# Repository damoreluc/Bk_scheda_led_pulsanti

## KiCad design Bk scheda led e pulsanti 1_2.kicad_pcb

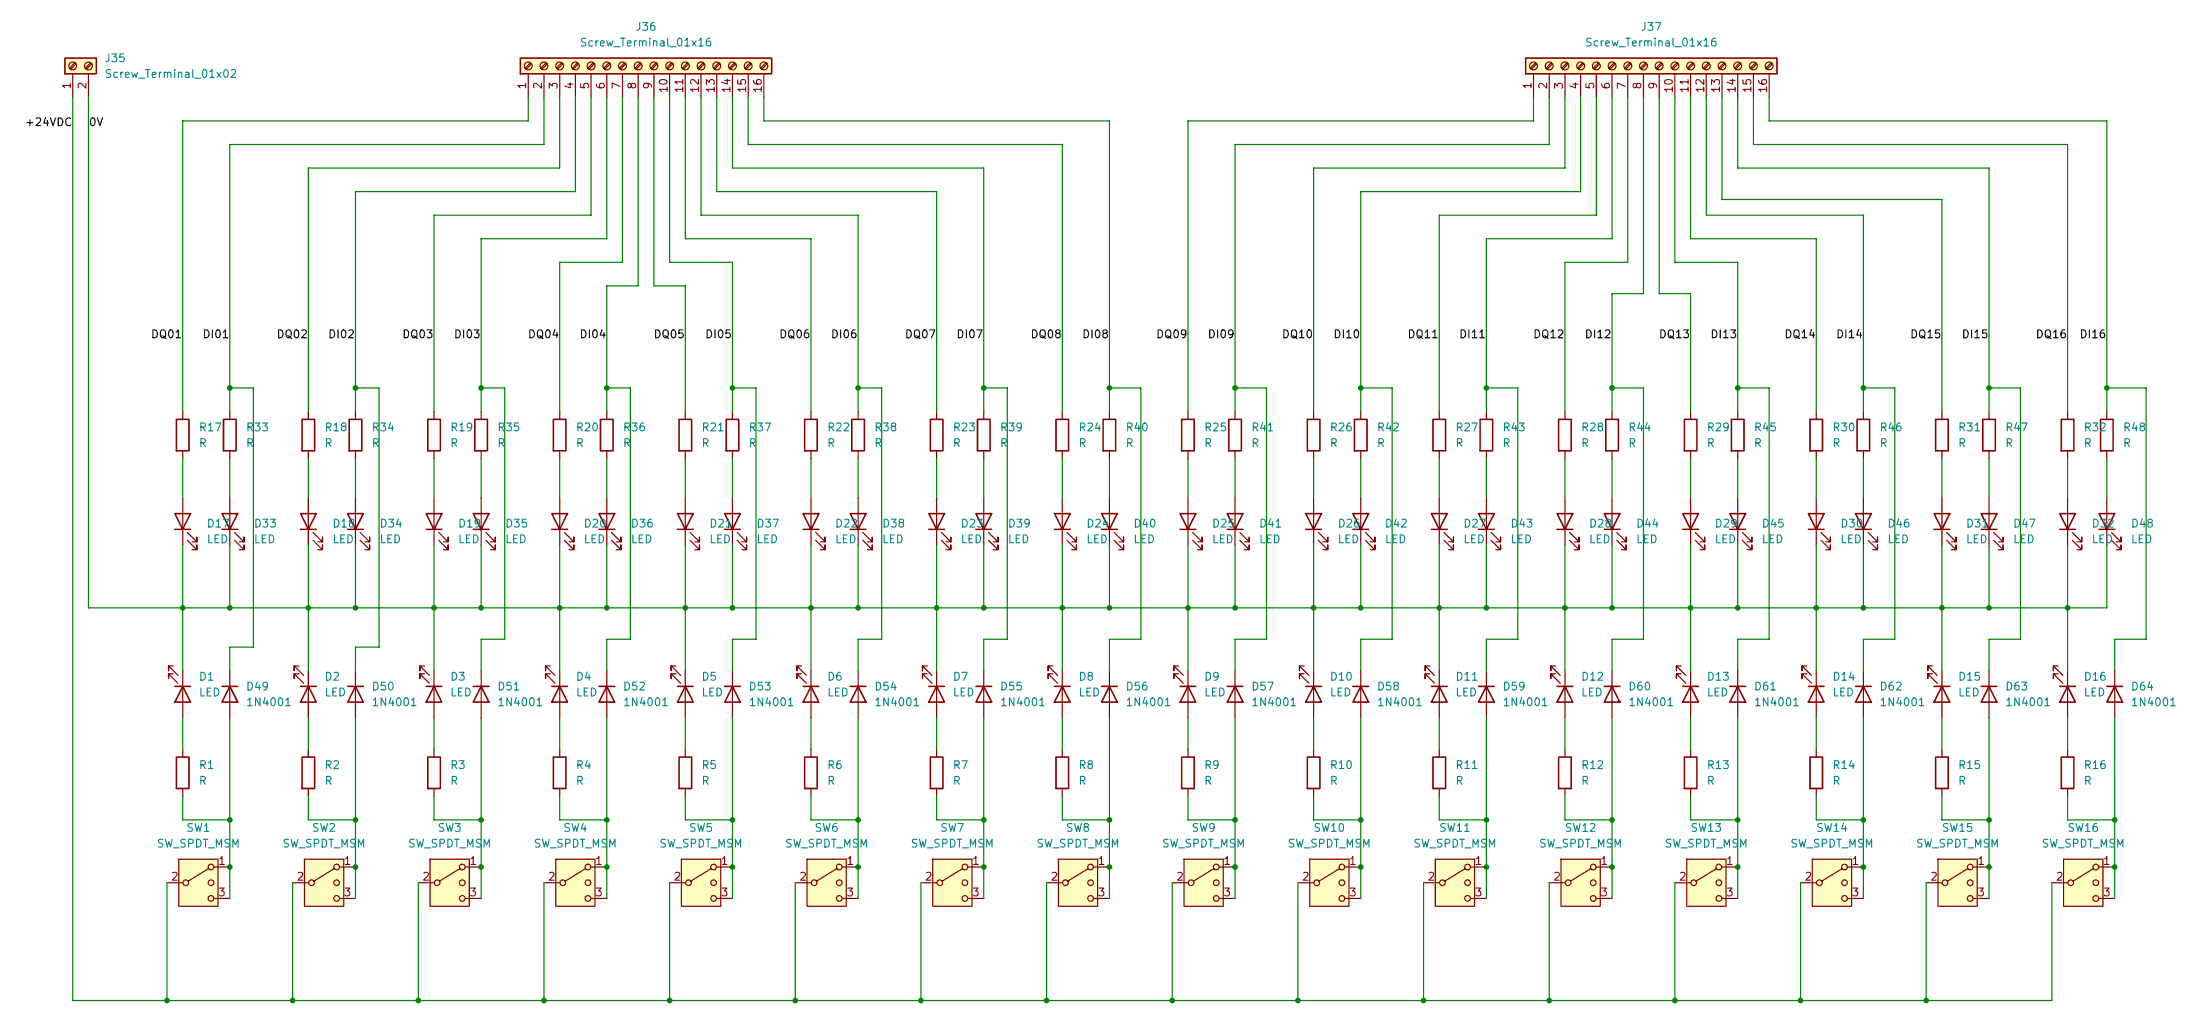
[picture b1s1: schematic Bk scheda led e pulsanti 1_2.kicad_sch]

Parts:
D1, D2, D3, D4, D5, D6, D7, D8, D9, D10, D11, D12, D13, D14, D15, D16, D17, D18, D19, D20, D21, D22, D23, D24, D25, D26, D27, D28, D29, D30, D31, D32, D33, D34, D35, D36, D37, D38, D39, D40, D41, D42, D43, D44, D45, D46, D47, D48: LED; LED_D5.0mm
D49, D50, D51, D52, D53, D54, D55, D56, D57, D58, D59, D60, D61, D62, D63, D64: 1N4001; D_DO-15_P12.70mm_Horizontal
J35: Screw_Terminal_01x02; TerminalBlock_Phoenix_PT-1,5-2-5.0-H_1x02_P5.00mm_Horizontal
J36, J37: Screw_Terminal_01x16; TerminalBlock_Phoenix_PT-1,5-16-5.0-H_1x16_P5.00mm_Horizont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
R1, R2, R3, R4, R5, R6, R7, R8, R9, R10, R11, R12, R13, R14, R15, R16, R17, R18, R19, R20, R21, R22, R23, R24, R25, R26, R27, R28, R29, R30, R31, R32, R33, R34, R35, R36, R37, R38, R39, R40, R41, R42, R43, R44, R45, R46, R47, R48: R; R_Axial_DIN0411_L9.9mm_D3.6mm_P12.70mm_Horizontal
SW1, SW2, SW3, SW4, SW5, SW6, SW7, SW8, SW9, SW10, SW11, SW12, SW13, SW14, SW15, SW16: SW_SPDT_MSM; SW_DEVIATORE_A_LEVETTAX03_D8X14_P4,70mm

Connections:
/0V: D1.1 (K), D2.1 (K), D3.1 (K), D4.1 (K), D5.1 (K), D6.1 (K), D7.1 (K), D8.1 (K), D9.1 (K), D10.1 (K), D11.1 (K), D12.1 (K), D13.1 (K), D14.1 (K), D15.1 (K), D16.1 (K), D17.1 (K), D18.1 (K), D19.1 (K), D20.1 (K), D21.1 (K), D22.1 (K), D23.1 (K), D24.1 (K), D25.1 (K), D26.1 (K), D27.1 (K), D28.1 (K), D29.1 (K), D30.1 (K), D31.1 (K), D32.1 (K), D33.1 (K), D34.1 (K), D35.1 (K), D36.1 (K), D37.1 (K), D38.1 (K), D39.1 (K), D40.1 (K), D41.1 (K), D42.1 (K), D43.1 (K), D44.1 (K), D45.1 (K), D46.1 (K), D47.1 (K), D48.1 (K), J35.2
/+24VDC: J35.1, SW1.2 (3), SW2.2 (3), SW3.2 (3), SW4.2 (3), SW5.2 (3), SW6.2 (3), SW7.2 (3), SW8.2 (3), SW9.2 (3), SW10.2 (3), SW11.2 (3), SW12.2 (3), SW13.2 (3), SW14.2 (3), SW15.2 (3), SW16.2 (3)
/DI01: D49.1 (K), J36.2, R33.1
/DI02: D50.1 (K), J36.4, R34.1
/DI03: D51.1 (K), J36.6, R35.1
/DI04: D52.1 (K), J36.8, R36.1
/DI05: D53.1 (K), J36.10, R37.1
/DI06: D54.1 (K), J36.12, R38.1
/DI07: D55.1 (K), J36.14, R39.1
/DI08: D56.1 (K), J36.16, R40.1
/DI09: D57.1 (K), J37.2, R41.1
/DI10: D58.1 (K), J37.4, R42.1
/DI11: D59.1 (K), J37.6, R43.1
/DI12: D60.1 (K), J37.8, R44.1
/DI13: D61.1 (K), J37.10, R45.1
/DI14: D62.1 (K), J37.12, R46.1
/DI15: D63.1 (K), J37.14, R47.1
/DI16: D64.1 (K), J37.16, R48.1
/DQ01: J36.1, R17.1
/DQ02: J36.3, R18.1
/DQ03: J36.5, R19.1
/DQ04: J36.7, R20.1
/DQ05: J36.9, R21.1
/DQ06: J36.11, R22.1
/DQ07: J36.13, R23.1
/DQ08: J36.15, R24.1
/DQ09: J37.1, R25.1
/DQ10: J37.3, R26.1
/DQ11: J37.5, R27.1
/DQ12: J37.7, R28.1
/DQ13: J37.9, R29.1
/DQ14: J37.11, R30.1
/DQ15: J37.13, R31.1
/DQ16: J37.15, R32.1
unnamed: D1.2 (A), R1.1
unnamed: D2.2 (A), R2.1
unnamed: D3.2 (A), R3.1
unnamed: D4.2 (A), R4.1
unnamed: D5.2 (A), R5.1
unnamed: D6.2 (A), R6.1
unnamed: D7.2 (A), R7.1
unnamed: D8.2 (A), R8.1
unnamed: D9.2 (A), R9.1
unnamed: D10.2 (A), R10.1
unnamed: D11.2 (A), R11.1
unnamed: D12.2 (A), R12.1
unnamed: D13.2 (A), R13.1
unnamed: D14.2 (A), R14.1
unnamed: D15.2 (A), R15.1
unnamed: D16.2 (A), R16.1
unnamed: D17.2 (A), R17.2
unnamed: D18.2 (A), R18.2
unnamed: D19.2 (A), R19.2
unnamed: D20.2 (A), R20.2
unnamed: D21.2 (A), R21.2
unnamed: D22.2 (A), R22.2
unnamed: D23.2 (A), R23.2
unnamed: D24.2 (A), R24.2
unnamed: D25.2 (A), R25.2
unnamed: D26.2 (A), R26.2
unnamed: D27.2 (A), R27.2
unnamed: D28.2 (A), R28.2
unnamed: D29.2 (A), R29.2
unnamed: D30.2 (A), R30.2
unnamed: D31.2 (A), R31.2
unnamed: D32.2 (A), R32.2
unnamed: D33.2 (A), R33.2
unnamed: D34.2 (A), R34.2
unnamed: D35.2 (A), R35.2
unnamed: D36.2 (A), R36.2
unnamed: D37.2 (A), R37.2
unnamed: D38.2 (A), R38.2
unnamed: D39.2 (A), R39.2
unnamed: D40.2 (A), R40.2
unnamed: D41.2 (A), R41.2
unnamed: D42.2 (A), R42.2
unnamed: D43.2 (A), R43.2
unnamed: D44.2 (A), R44.2
unnamed: D45.2 (A), R45.2
unnamed: D46.2 (A), R46.2
unnamed: D47.2 (A), R47.2
unnamed: D48.2 (A), R48.2
unnamed: D49.2 (A), R1.2, SW1.1, SW1.3 (4)
unnamed: D50.2 (A), R2.2, SW2.1, SW2.3 (4)
unnamed: D51.2 (A), R3.2, SW3.1, SW3.3 (4)
unnamed: D52.2 (A), R4.2, SW4.1, SW4.3 (4)
unnamed: D53.2 (A), R5.2, SW5.1, SW5.3 (4)
unnamed: D54.2 (A), R6.2, SW6.1, SW6.3 (4)
unnamed: D55.2 (A), R7.2, SW7.1, SW7.3 (4)
unnamed: D56.2 (A), R8.2, SW8.1, SW8.3 (4)
unnamed: D57.2 (A), R9.2, SW9.1, SW9.3 (4)
unnamed: D58.2 (A), R10.2, SW10.1, SW10.3 (4)
unnamed: D59.2 (A), R11.2, SW11.1, SW11.3 (4)
unnamed: D60.2 (A), R12.2, SW12.1, SW12.3 (4)
unnamed: D61.2 (A), R13.2, SW13.1, SW13.3 (4)
unnamed: D62.2 (A), R14.2, SW14.1, SW14.3 (4)
unnamed: D63.2 (A), R15.2, SW15.1, SW15.3 (4)
unnamed: D64.2 (A), R16.2, SW16.1, SW16.3 (4)

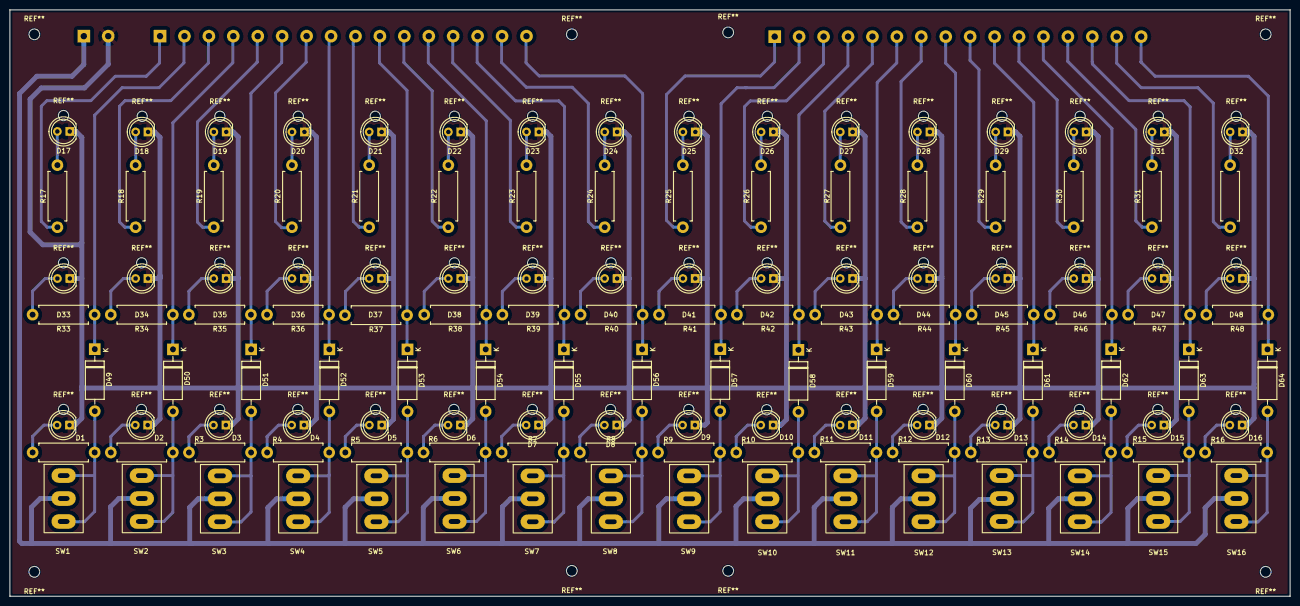
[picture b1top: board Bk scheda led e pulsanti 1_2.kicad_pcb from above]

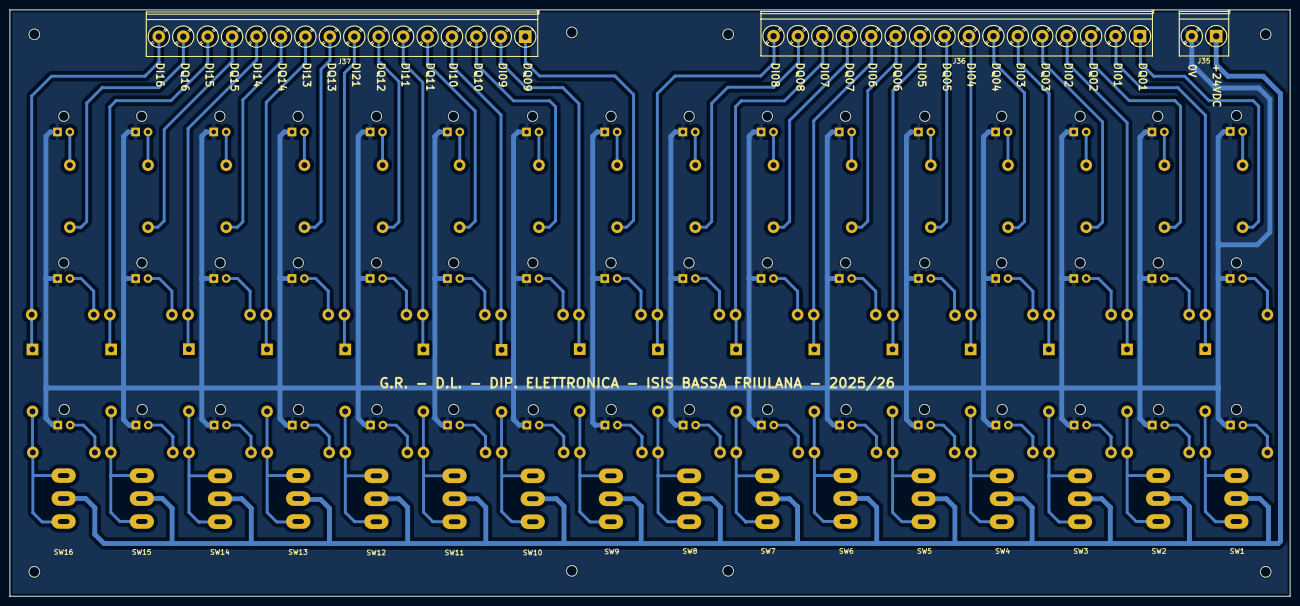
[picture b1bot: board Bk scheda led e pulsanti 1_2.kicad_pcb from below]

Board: 2 copper layers, 262.0 x 120.0 mm, 131 parts (3 on the bottom side), 98 nets.

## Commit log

2026-01-31 Base: schema e pcb iniziali
2026-01-31 Aggiunto pdf dello schema e rendering 3D del PCB
2026-01-31 Modifica intitolazione su PCB
